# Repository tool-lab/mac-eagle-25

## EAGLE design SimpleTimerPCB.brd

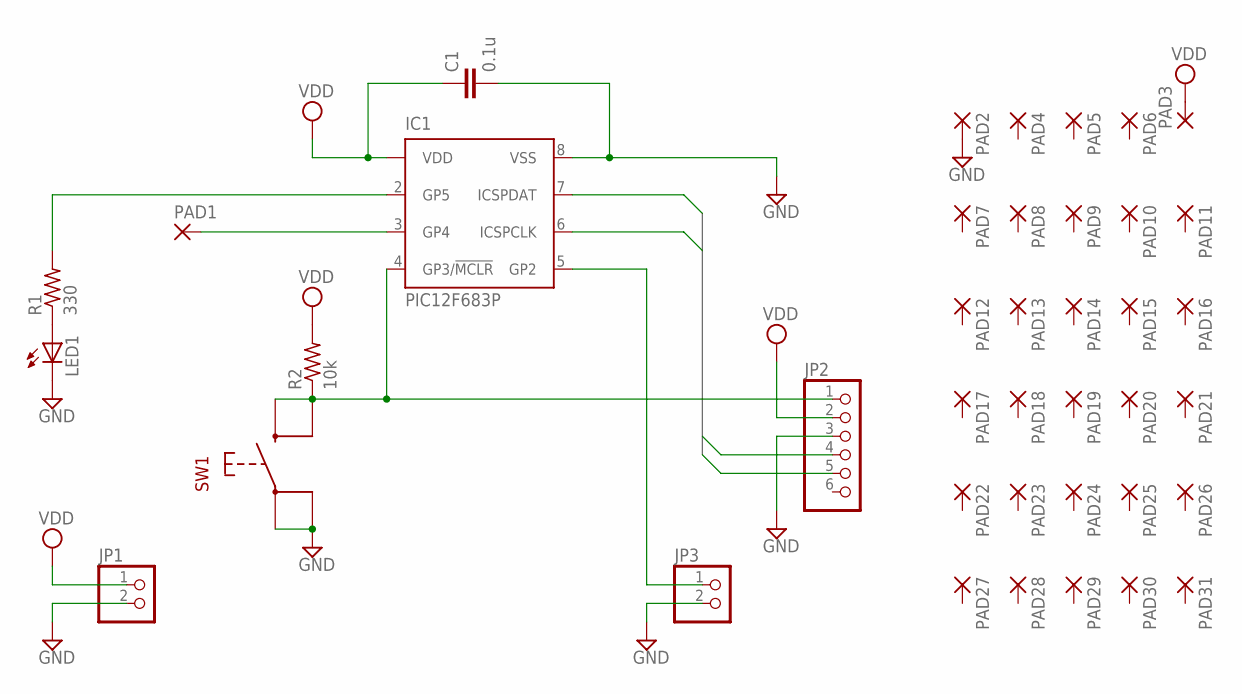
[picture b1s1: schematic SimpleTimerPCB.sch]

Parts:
C1: 0.1u; C050-024X044
IC1: PIC12F683P; DIL8
JP1, JP3: PINHD-1X2; 1X02
JP2: PINHD-1X6; 1X06
LED1: LED3MM
PAD1, PAD2, PAD3, PAD4, PAD5, PAD6, PAD7, PAD8, PAD9, PAD10, PAD11, PAD12, PAD13, PAD14, PAD15, PAD16, PAD17, PAD18, PAD19, PAD20, PAD21, PAD22, PAD23, PAD24, PAD25, PAD26, PAD27, PAD28, PAD29, PAD30, PAD31: 1,6/0,9
R1: 330; 0204/7
R2: 10k; 0204/7
SW1: TACT-SWITCH; TACTSW-25X20

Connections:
GND: C1.2, IC1.8 (VSS), JP1.2, JP2.3, JP3.2, LED1.K (C), PAD2.1, SW1.3 (P1), SW1.4 (P2)
unnamed: LED1.A, R1.1
unnamed: IC1.4 (GP3/!MCLR!), JP2.1, R2.1, SW1.1 (S1), SW1.2 (S2)
unnamed: IC1.3 (GP4), PAD1.1
unnamed: IC1.2 (GP5), R1.2
unnamed: IC1.5 (GP2), JP3.1
PIN4: IC1.7 (ICSPDAT), JP2.4
PIN5: IC1.6 (ICSPCLK), JP2.5
VDD: C1.1, IC1.1 (VDD), JP1.1, JP2.2, PAD3.1, R2.2

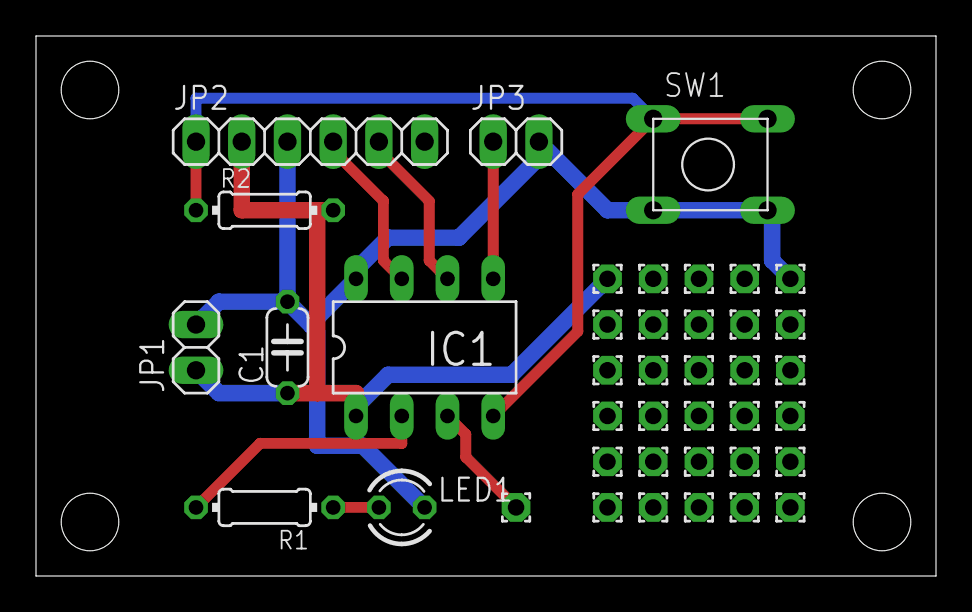
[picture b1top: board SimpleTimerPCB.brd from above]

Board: 2 copper layers, 50.0 x 30.0 mm, 40 parts (0 on the bottom side), 9 nets.
